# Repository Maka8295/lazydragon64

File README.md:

# Lazy Dragon 64

## Features

- 32 keys per half (64 total), column-staggered, with a 1.5U thumb key
- One reversible PCB for both halves
- Hot-swap MX sockets
- Per-key RGB
- RP2040-Zero controller
- 0.91" 128 × 32 OLED
- USB-C split link
- QMK firmware
- 4-layer, 1.6 mm PCB
- Corne-style mounting

## BOM

| Qty | Part |
|---:|---|
| 2 | PCB (`production/`) |
| 2 | 1.6 mm FR4 plate (`plate/production/`) |
| 2 | Case (`case-final/`) |
| 2 | RP2040-Zero |
| 2 | 0.91" 128 × 32 I2C OLED |
| 64 | MX hot-swap socket, CPG151101S11 |
| 64 | SK6812MINI-E |
| 64 | 1N4148W, SOD-123 |
| 64 | 100 nF 0805 |
| 2 | 1 µF 0805 |
| 2 | USB-C receptacle, 16-pin |
| 54 | 2.54 mm machined female socket |
| 54 | 2.54 mm male pin |
| 8 | M2 × 8 mm standoff |
| 16 | M2 × 4 mm screw |
| 64 | MX switch and keycap (62 × 1U, 2 × 1.5U) |
| 1 | USB-C cable |

## Install

| | RP2040-Zero, J1, J2 | Other parts | Bridge |
|---|---|---|---|
| Left | F | B | JP1, JP2, JP8, JP10, JP12, JP14 |
| Right | B | F | JP4, JP5, JP7, JP9, JP11, JP13 |

1. Bridge the jumpers. Solder the diodes, capacitors, LEDs (angled corner on the square pad) and hot-swap sockets. Fit C1 on one face only.
2. Solder J1, the RP2040-Zero's sockets and J2.
3. Hold BOOT and plug the RP2040-Zero in. Copy `firmware/lazydragon64_left.uf2` or `lazydragon64_right.uf2` to the `RPI-RP2` drive.
4. Plug in the RP2040-Zero and the OLED.
5. Screw the standoffs to the case floor. Clip the switches into the plate, press the PCB onto them, set it in the case and screw the plate on.
6. Join the halves with a USB-C cable between the J1 ports. Plug the computer into either RP2040-Zero.

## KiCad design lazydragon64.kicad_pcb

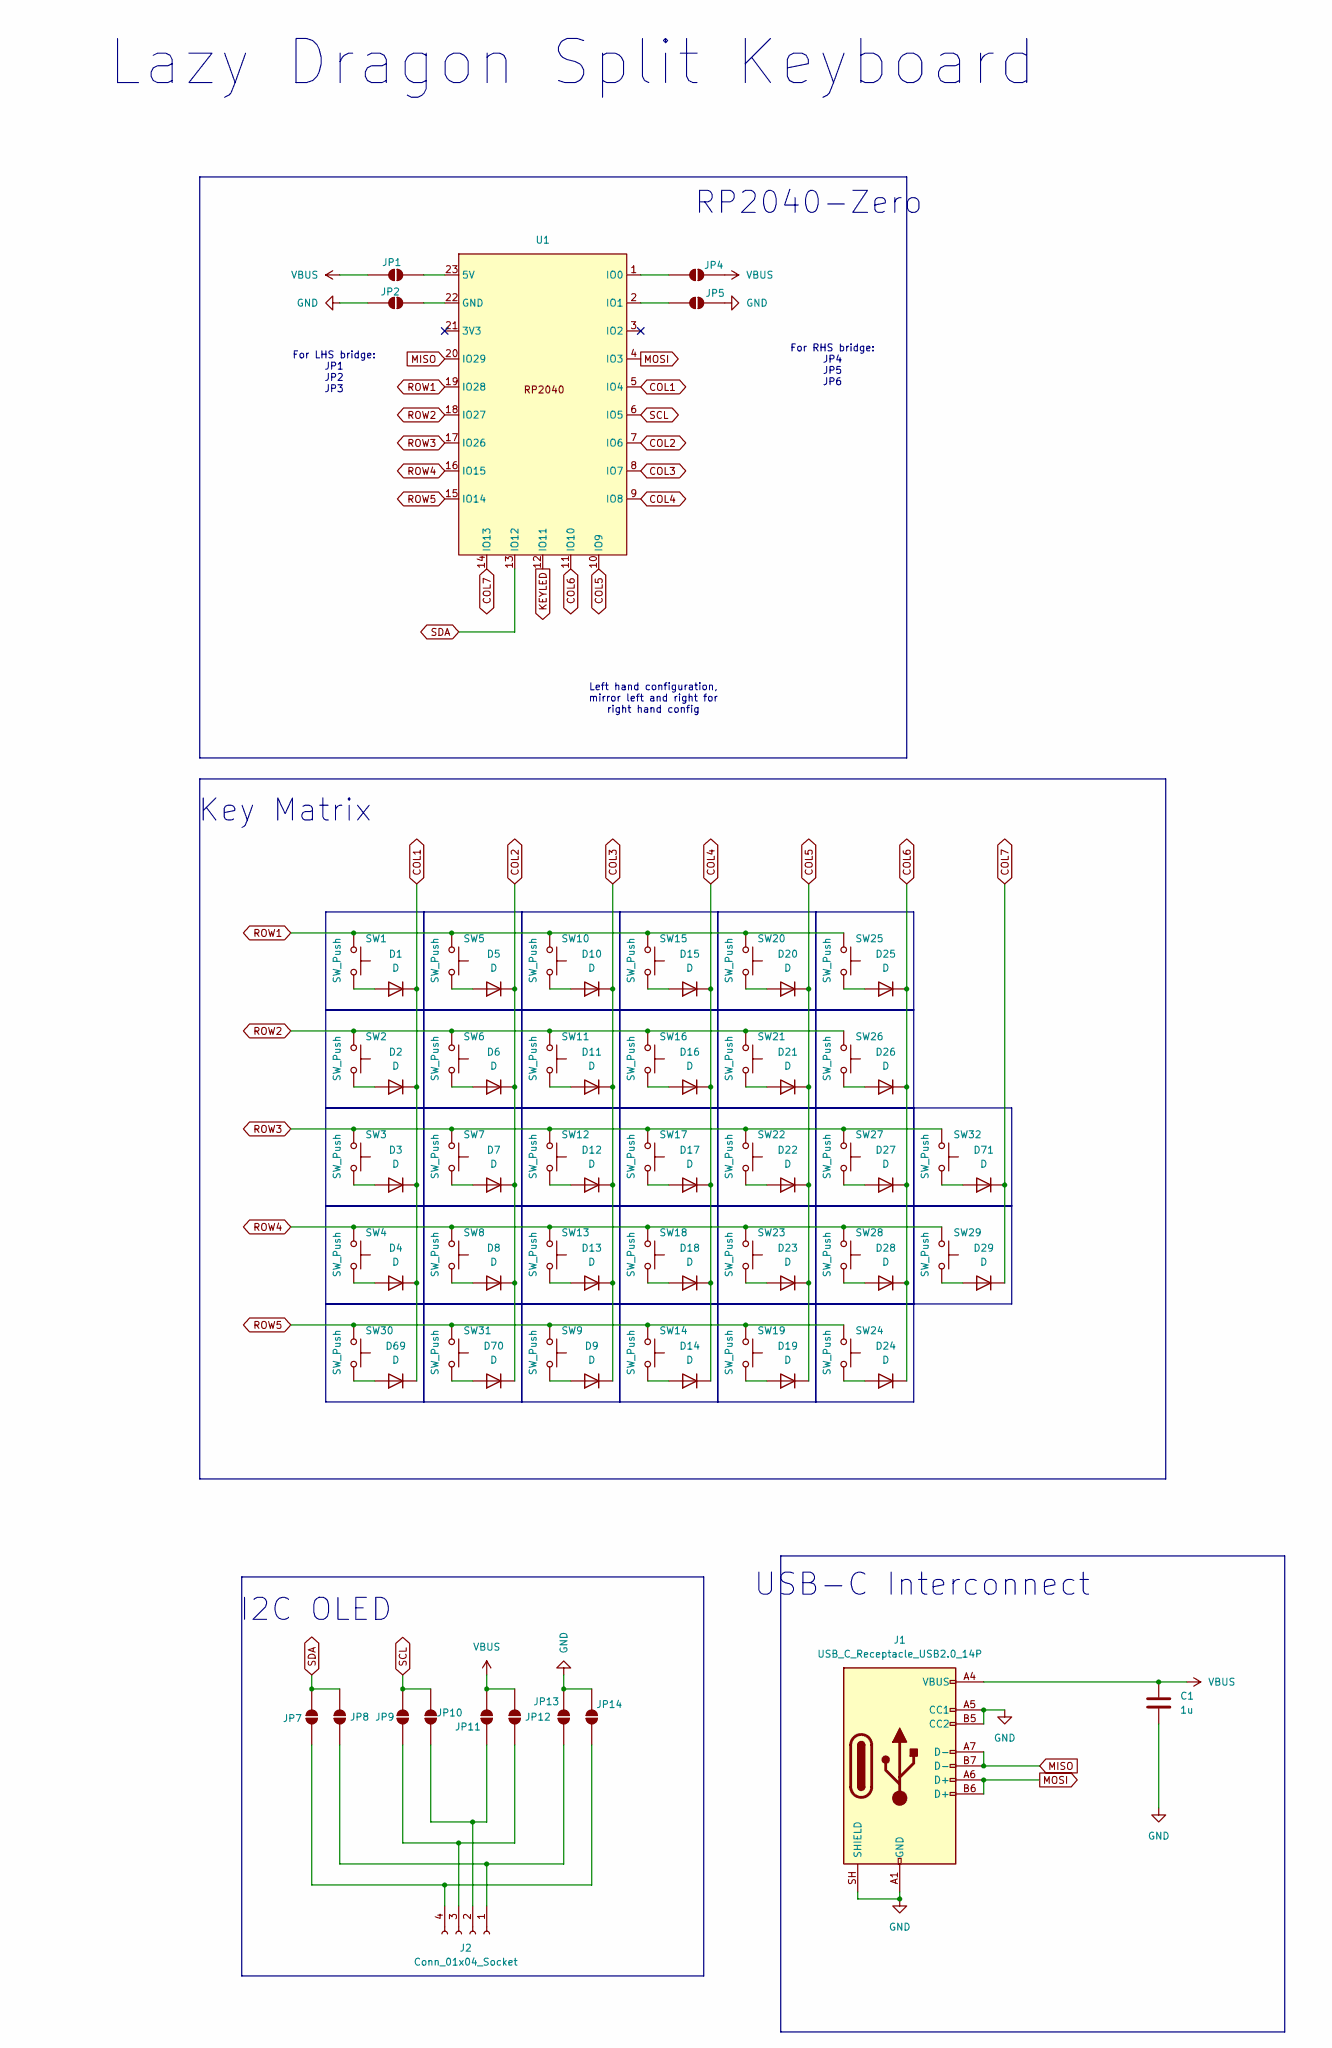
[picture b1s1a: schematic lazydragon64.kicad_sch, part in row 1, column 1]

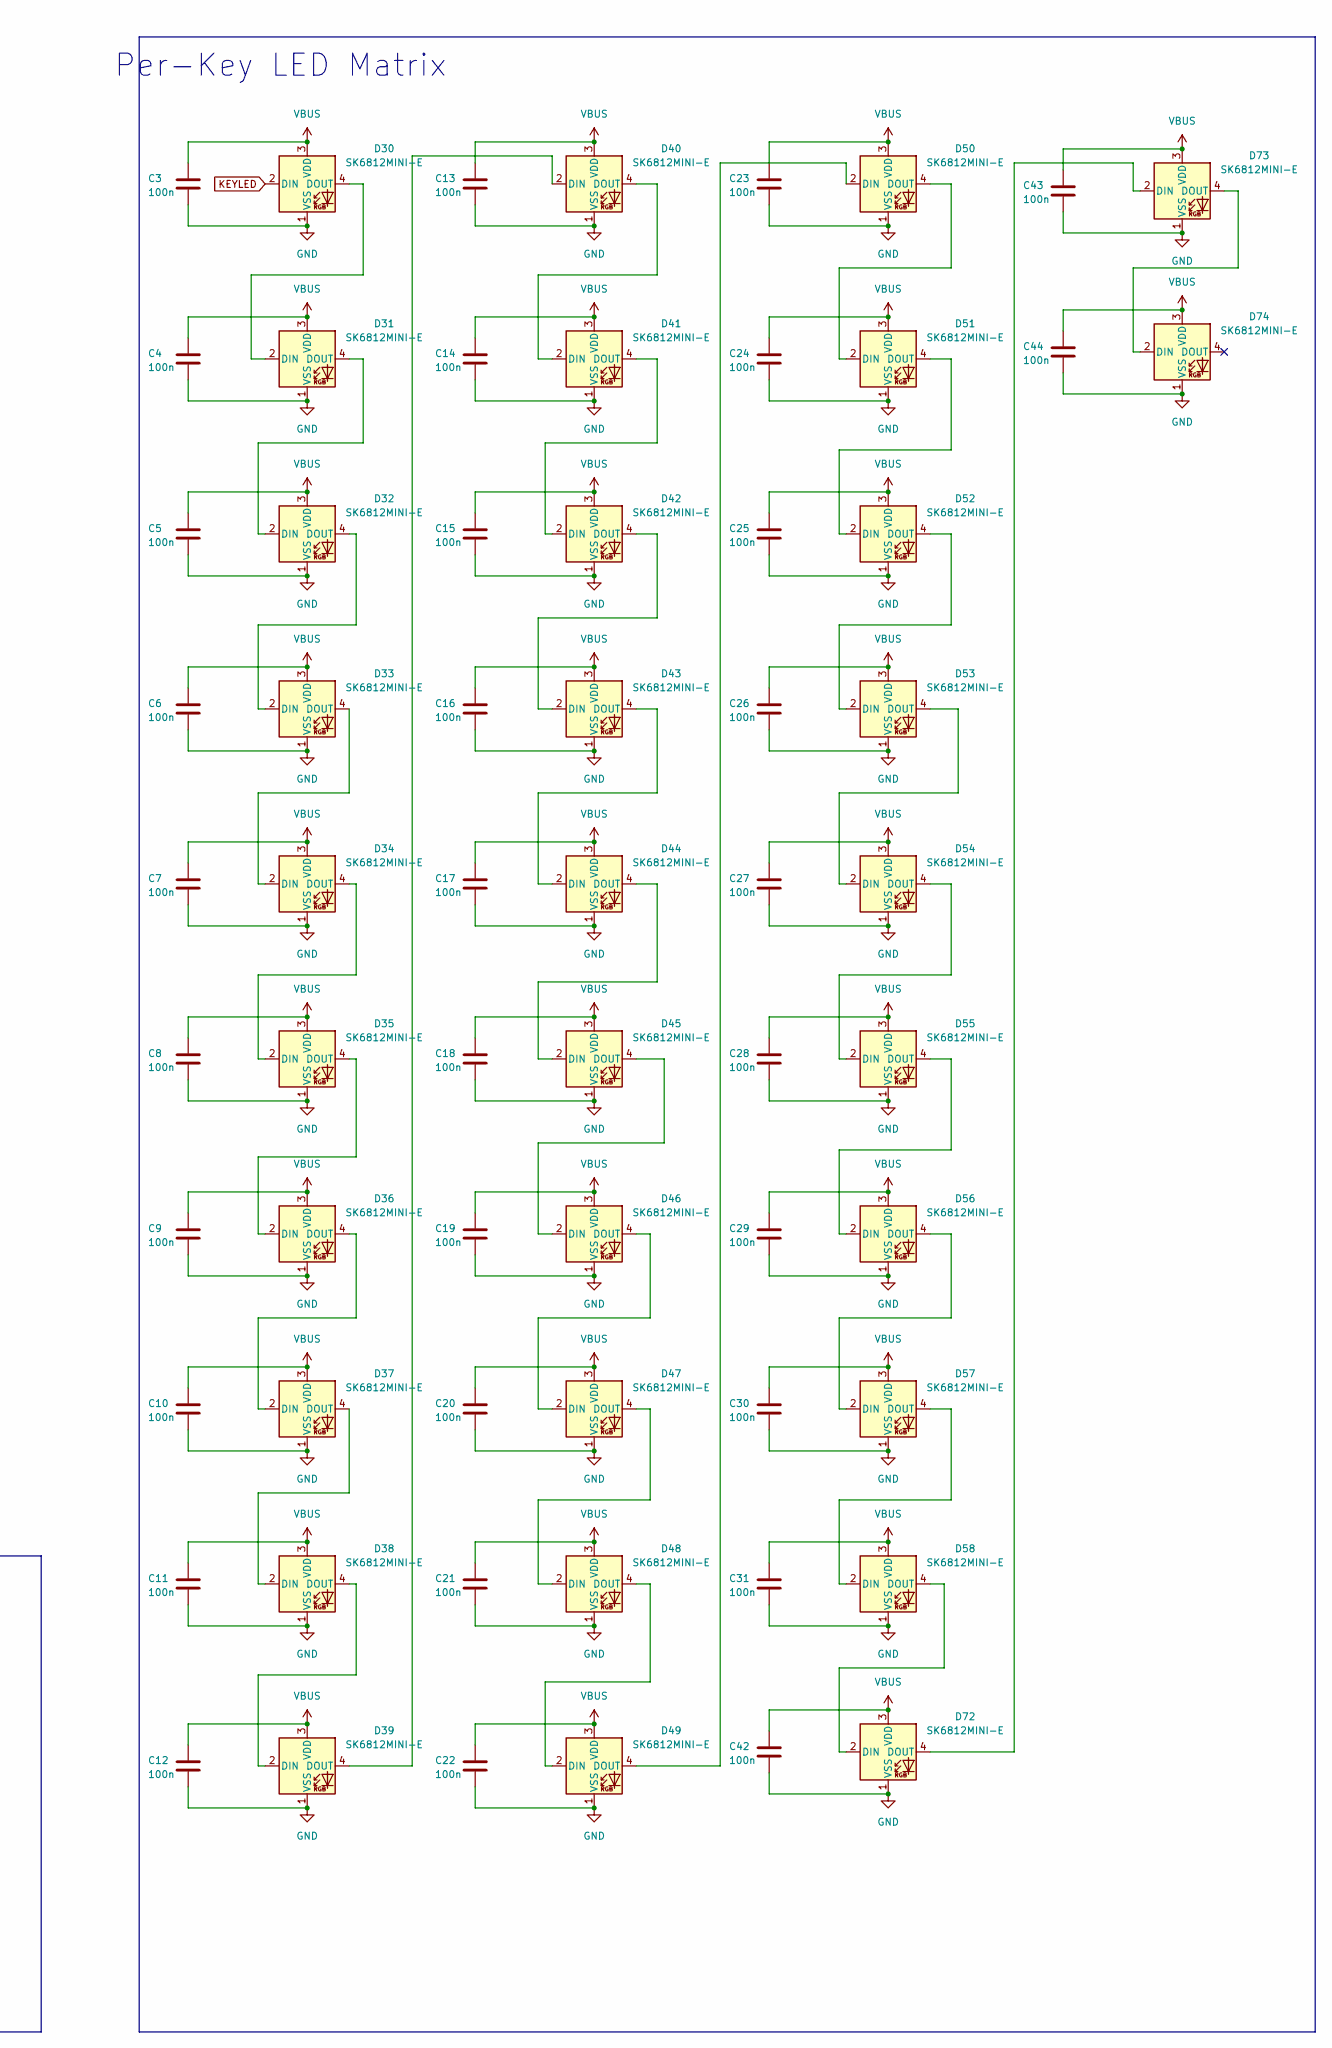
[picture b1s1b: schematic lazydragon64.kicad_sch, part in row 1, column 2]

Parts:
C1: 1u; C_0805_2012Metric_Pad1.18x1.45mm_HandSolder
C3, C4, C5, C6, C7, C8, C9, C10, C11, C12, C13, C14, C15, C16, C17, C18, C19, C20, C21, C22, C23, C24, C25, C26, C27, C28, C29, C30, C31, C42, C43, C44: 100n; C_0805_Reversible
D1, D2, D3, D4, D5, D6, D7, D8, D9, D10, D11, D12, D13, D14, D15, D16, D17, D18, D19, D20, D21, D22, D23, D24, D25, D26, D27, D28, D29, D69, D70, D71: D; D_SOD-123_reversible
D30, D31, D32, D33, D34, D35, D36, D37, D38, D39, D40, D41, D42, D43, D44, D45, D46, D47, D48, D49, D50, D51, D52, D53, D54, D55, D56, D57, D58, D72, D73, D74: SK6812MINI-E; LED_SK6812MINI-E_3.2x2.8mm_P1.5mm_ReverseMount
J1: USB_C_Receptacle_USB2.0_14P; USB_C_Receptacle_reversible
J2: Conn_01x04_Socket; PinHeader_1x04_P2.54mm_Vertical
JP1, JP2, JP4, JP5, JP7, JP8, JP9, JP10, JP11, JP12, JP13, JP14: SolderJumper_2_Open; SolderJumper-2_P1.3mm_Open_RoundedPad1.0x1.5mm
SW1, SW2, SW3, SW4, SW5, SW6, SW7, SW8, SW9, SW10, SW11, SW12, SW13, SW14, SW15, SW16, SW17, SW18, SW19, SW20, SW21, SW22, SW23, SW25, SW26, SW27, SW28, SW29, SW30, SW31, SW32: SW_Push; hotswap_reversible
SW24: SW_Push; hotswap_reversible_1.5U
U1: MODULE_RP2040-ZERO_1

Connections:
COL1: D1.1 (K), D2.1 (K), D3.1 (K), D4.1 (K), D69.1 (K), U1.5 (IO4)
COL2: D5.1 (K), D6.1 (K), D7.1 (K), D8.1 (K), D70.1 (K), U1.7 (IO6)
COL3: D9.1 (K), D10.1 (K), D11.1 (K), D12.1 (K), D13.1 (K), U1.8 (IO7)
COL4: D14.1 (K), D15.1 (K), D16.1 (K), D17.1 (K), D18.1 (K), U1.9 (IO8)
COL5: D19.1 (K), D20.1 (K), D21.1 (K), D22.1 (K), D23.1 (K), U1.10 (IO9)
COL6: D24.1 (K), D25.1 (K), D26.1 (K), D27.1 (K), D28.1 (K), U1.11 (IO10)
COL7: D29.1 (K), D71.1 (K), U1.14 (IO13)
GND: C1.2, C3.2, C4.2, C5.2, C6.2, C7.2, C8.2, C9.2, C10.2, C11.2, C12.2, C13.2, C14.2, C15.2, C16.2, C17.2, C18.2, C19.2, C20.2, C21.2, C22.2, C23.2, C24.2, C25.2, C26.2, C27.2, C28.2, C29.2, C30.2, C31.2, C42.2, C43.2, C44.2, D30.1 (VSS), D31.1 (VSS), D32.1 (VSS), D33.1 (VSS), D34.1 (VSS), D35.1 (VSS), D36.1 (VSS), D37.1 (VSS), D38.1 (VSS), D39.1 (VSS), D40.1 (VSS), D41.1 (VSS), D42.1 (VSS), D43.1 (VSS), D44.1 (VSS), D45.1 (VSS), D46.1 (VSS), D47.1 (VSS), D48.1 (VSS), D49.1 (VSS), D50.1 (VSS), D51.1 (VSS), D52.1 (VSS), D53.1 (VSS), D54.1 (VSS), D55.1 (VSS), D56.1 (VSS), D57.1 (VSS), D58.1 (VSS), D72.1 (VSS), D73.1 (VSS), D74.1 (VSS), J1.A1 (GND), J1.A5 (CC1), J1.A12 (GND), J1.B1 (GND), J1.B5 (CC2), J1.B12 (GND), J1.SH (SHIELD), JP2.1 (A), JP5.2 (B), JP13.1 (A), JP14.1 (A); also elsewhere on the board
KEYLED: D30.2 (DIN), U1.12 (IO11)
MISO: J1.A7 (D-), J1.B7 (D-), U1.20 (IO29)
MOSI: J1.A6 (D+), J1.B6 (D+), U1.4 (IO3)
unnamed: D1.2 (A), SW1.2
unnamed: D2.2 (A), SW2.2
unnamed: D3.2 (A), SW3.2
unnamed: D4.2 (A), SW4.2
unnamed: D5.2 (A), SW5.2
unnamed: D6.2 (A), SW6.2
unnamed: D7.2 (A), SW7.2
unnamed: D8.2 (A), SW8.2
unnamed: D9.2 (A), SW9.2
unnamed: D10.2 (A), SW10.2
unnamed: D11.2 (A), SW11.2
unnamed: D12.2 (A), SW12.2
unnamed: D13.2 (A), SW13.2
unnamed: D14.2 (A), SW14.2
unnamed: D15.2 (A), SW15.2
unnamed: D16.2 (A), SW16.2
unnamed: D17.2 (A), SW17.2
unnamed: D18.2 (A), SW18.2
unnamed: D19.2 (A), SW19.2
unnamed: D20.2 (A), SW20.2
unnamed: D21.2 (A), SW21.2
unnamed: D22.2 (A), SW22.2
unnamed: D23.2 (A), SW23.2
unnamed: D24.2 (A), SW24.2
unnamed: D25.2 (A), SW25.2
unnamed: D26.2 (A), SW26.2
unnamed: D27.2 (A), SW27.2
unnamed: D28.2 (A), SW28.2
unnamed: D29.2 (A), SW29.2
unnamed: D30.4 (DOUT), D31.2 (DIN)
unnamed: D31.4 (DOUT), D32.2 (DIN)
unnamed: D32.4 (DOUT), D33.2 (DIN)
unnamed: D33.4 (DOUT), D34.2 (DIN)
unnamed: D34.4 (DOUT), D35.2 (DIN)
unnamed: D35.4 (DOUT), D36.2 (DIN)
unnamed: D36.4 (DOUT), D37.2 (DIN)
unnamed: D37.4 (DOUT), D38.2 (DIN)
unnamed: D38.4 (DOUT), D39.2 (DIN)
unnamed: D39.4 (DOUT), D40.2 (DIN)
unnamed: D40.4 (DOUT), D41.2 (DIN)
unnamed: D41.4 (DOUT), D42.2 (DIN)
unnamed: D42.4 (DOUT), D43.2 (DIN)
unnamed: D43.4 (DOUT), D44.2 (DIN)
unnamed: D44.4 (DOUT), D45.2 (DIN)
unnamed: D45.4 (DOUT), D46.2 (DIN)
unnamed: D46.4 (DOUT), D47.2 (DIN)
unnamed: D47.4 (DOUT), D48.2 (DIN)
unnamed: D48.4 (DOUT), D49.2 (DIN)
unnamed: D49.4 (DOUT), D50.2 (DIN)
unnamed: D50.4 (DOUT), D51.2 (DIN)
unnamed: D51.4 (DOUT), D52.2 (DIN)
unnamed: D52.4 (DOUT), D53.2 (DIN)
unnamed: D53.4 (DOUT), D54.2 (DIN)
unnamed: D54.4 (DOUT), D55.2 (DIN)
unnamed: D55.4 (DOUT), D56.2 (DIN)
unnamed: D56.4 (DOUT), D57.2 (DIN)
unnamed: D57.4 (DOUT), D58.2 (DIN)
unnamed: D58.4 (DOUT), D72.2 (DIN)
unnamed: D69.2 (A), SW30.2
unnamed: D70.2 (A), SW31.2
unnamed: D71.2 (A), SW32.2
unnamed: D72.4 (DOUT), D73.2 (DIN)
unnamed: D73.4 (DOUT), D74.2 (DIN)
unnamed: J2.1, JP8.2 (B), JP13.2 (B)
unnamed: J2.2, JP10.2 (B), JP11.2 (B)
unnamed: J2.3, JP9.2 (B), JP12.2 (B)
unnamed: J2.4, JP7.2 (B), JP14.2 (B)
unnamed: JP1.2 (B), U1.23 (5V)
unnamed: JP2.2 (B), U1.22 (GND)
unnamed: JP4.1 (A), U1.1 (IO0)
unnamed: JP5.1 (A), U1.2 (IO1)
ROW1: SW1.1, SW5.1, SW10.1, SW15.1, SW20.1, SW25.1, U1.19 (IO28)
ROW2: SW2.1, SW6.1, SW11.1, SW16.1, SW21.1, SW26.1, U1.18 (IO27)
ROW3: SW3.1, SW7.1, SW12.1, SW17.1, SW22.1, SW27.1, SW32.1, U1.17 (IO26)
ROW4: SW4.1, SW8.1, SW13.1, SW18.1, SW23.1, SW28.1, SW29.1, U1.16 (IO15)
ROW5: SW9.1, SW14.1, SW19.1, SW24.1, SW30.1, SW31.1, U1.15 (IO14)
SCL: JP9.1 (A), JP10.1 (A), U1.6 (IO5)
SDA: JP7.1 (A), JP8.1 (A), U1.13 (IO12)
VBUS: C1.1, C3.1, C4.1, C5.1, C6.1, C7.1, C8.1, C9.1, C10.1, C11.1, C12.1, C13.1, C14.1, C15.1, C16.1, C17.1, C18.1, C19.1, C20.1, C21.1, C22.1, C23.1, C24.1, C25.1, C26.1, C27.1, C28.1, C29.1, C30.1, C31.1, C42.1, C43.1, C44.1, D30.3 (VDD), D31.3 (VDD), D32.3 (VDD), D33.3 (VDD), D34.3 (VDD), D35.3 (VDD), D36.3 (VDD), D37.3 (VDD), D38.3 (VDD), D39.3 (VDD), D40.3 (VDD), D41.3 (VDD), D42.3 (VDD), D43.3 (VDD), D44.3 (VDD), D45.3 (VDD), D46.3 (VDD), D47.3 (VDD), D48.3 (VDD), D49.3 (VDD), D50.3 (VDD), D51.3 (VDD), D52.3 (VDD), D53.3 (VDD), D54.3 (VDD), D55.3 (VDD), D56.3 (VDD), D57.3 (VDD), D58.3 (VDD), D72.3 (VDD), D73.3 (VDD), D74.3 (VDD), J1.A4 (VBUS), J1.A9 (VBUS), J1.B4 (VBUS), J1.B9 (VBUS), JP1.1 (A), JP4.2 (B), JP11.1 (A), JP12.1 (A); also elsewhere on the board

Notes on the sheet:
I2C OLED
Left hand configuration, mirror left and right for right hand config
USB-C Interconnect
For RHS bridge: JP4 JP5 JP6
Key Matrix
Lazy Dragon Split Keyboard
Per-Key LED Matrix
For LHS bridge: JP1 JP2 JP3
RP2040-Zero

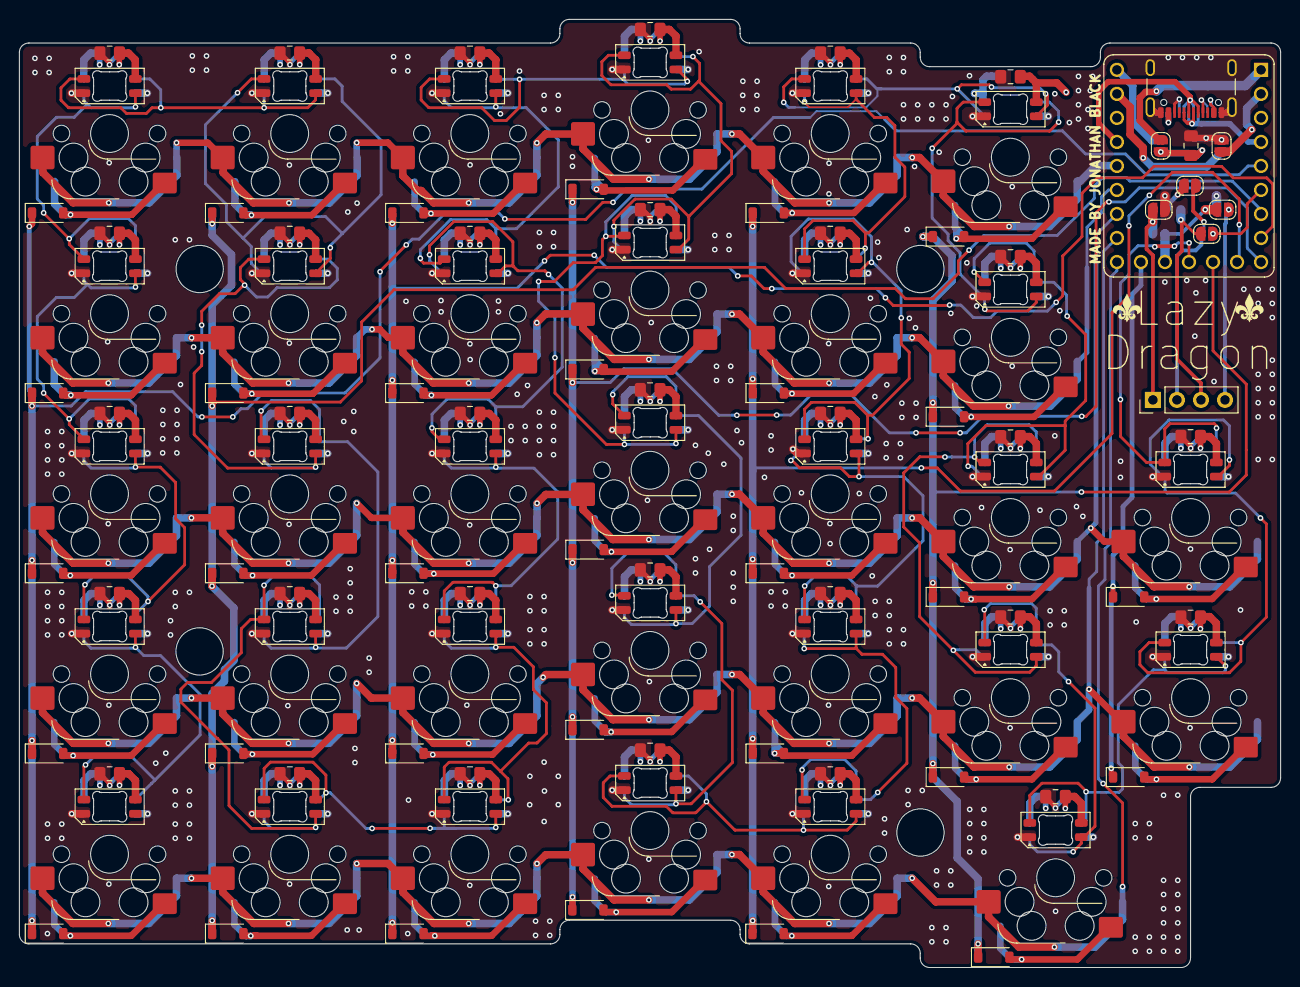
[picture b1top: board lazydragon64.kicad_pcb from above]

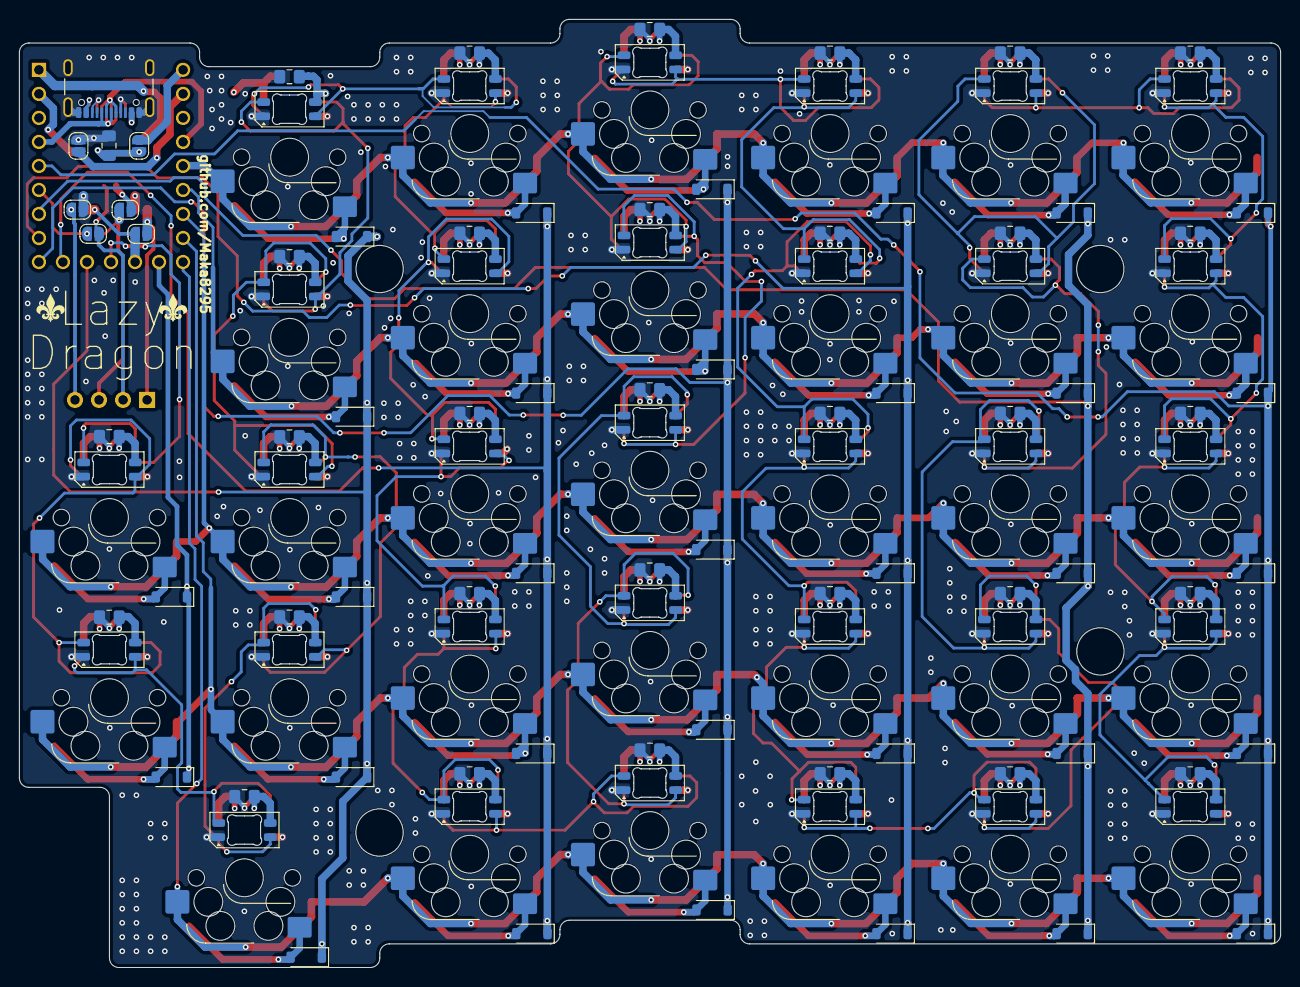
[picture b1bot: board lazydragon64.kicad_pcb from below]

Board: 4 copper layers, 133.4 x 100.2 mm, 149 parts (7 on the bottom side), 90 nets.

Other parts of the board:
C1#2: 1u; C_0805_2012Metric_Pad1.18x1.45mm_HandSolder
H1, H2, H3, H4: MountingHole_5.0mm_Spacer

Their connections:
GND: C1#2.2; also elsewhere on the board
VBUS: C1#2.1; also elsewhere on the board

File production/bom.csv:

Designator,Footprint,Quantity,Value,LCSC Part #
"C1_2, C1",0805,2,1u,
"C10, C11, C12, C13, C14, C15, C16, C17, C18, C19, C20, C21, C22, C23, C24, C25, C26, C27, C28, C29, C3, C30, C31, C4, C42, C43, C44, C5, C6, C7, C8, C9",C_0805_Reversible,32,100n,
"D1, D10, D11, D12, D13, D14, D15, D16, D17, D18, D19, D2, D20, D21, D22, D23, D24, D25, D26, D27, D28, D29, D3, D4, D5, D6, D69, D7, D70, D71, D8, D9",D_SOD-123_reversible,32,D,
"D30, D31, D32, D33, D34, D35, D36, D37, D38, D39, D40, D41, D42, D43, D44, D45, D46, D47, D48, D49, D50, D51, D52, D53, D54, D55, D56, D57, D58, D72, D73, D74",LED_SK6812MINI-E_3.2x2.8mm_P1.5mm_ReverseMount,32,SK6812MINI-E,
J1,USB_C_Receptacle_reversible,1,USB_C_Receptacle_USB2.0_14P,
J2,PinHeader_1x04_P2.54mm_Vertical,1,Conn_01x04_Socket,
"SW1, SW10, SW11, SW12, SW13, SW14, SW15, SW16, SW17, SW18, SW19, SW2, SW20, SW21, SW22, SW23, SW25, SW26, SW27, SW28, SW29, SW3, SW30, SW31, SW32, SW4, SW5, SW6, SW7, SW8, SW9",hotswap_reversible,31,SW_Push,
SW24,hotswap_reversible_1.5U,1,SW_Push,
U1,MODULE_RP2040-ZERO_1,1,~,
